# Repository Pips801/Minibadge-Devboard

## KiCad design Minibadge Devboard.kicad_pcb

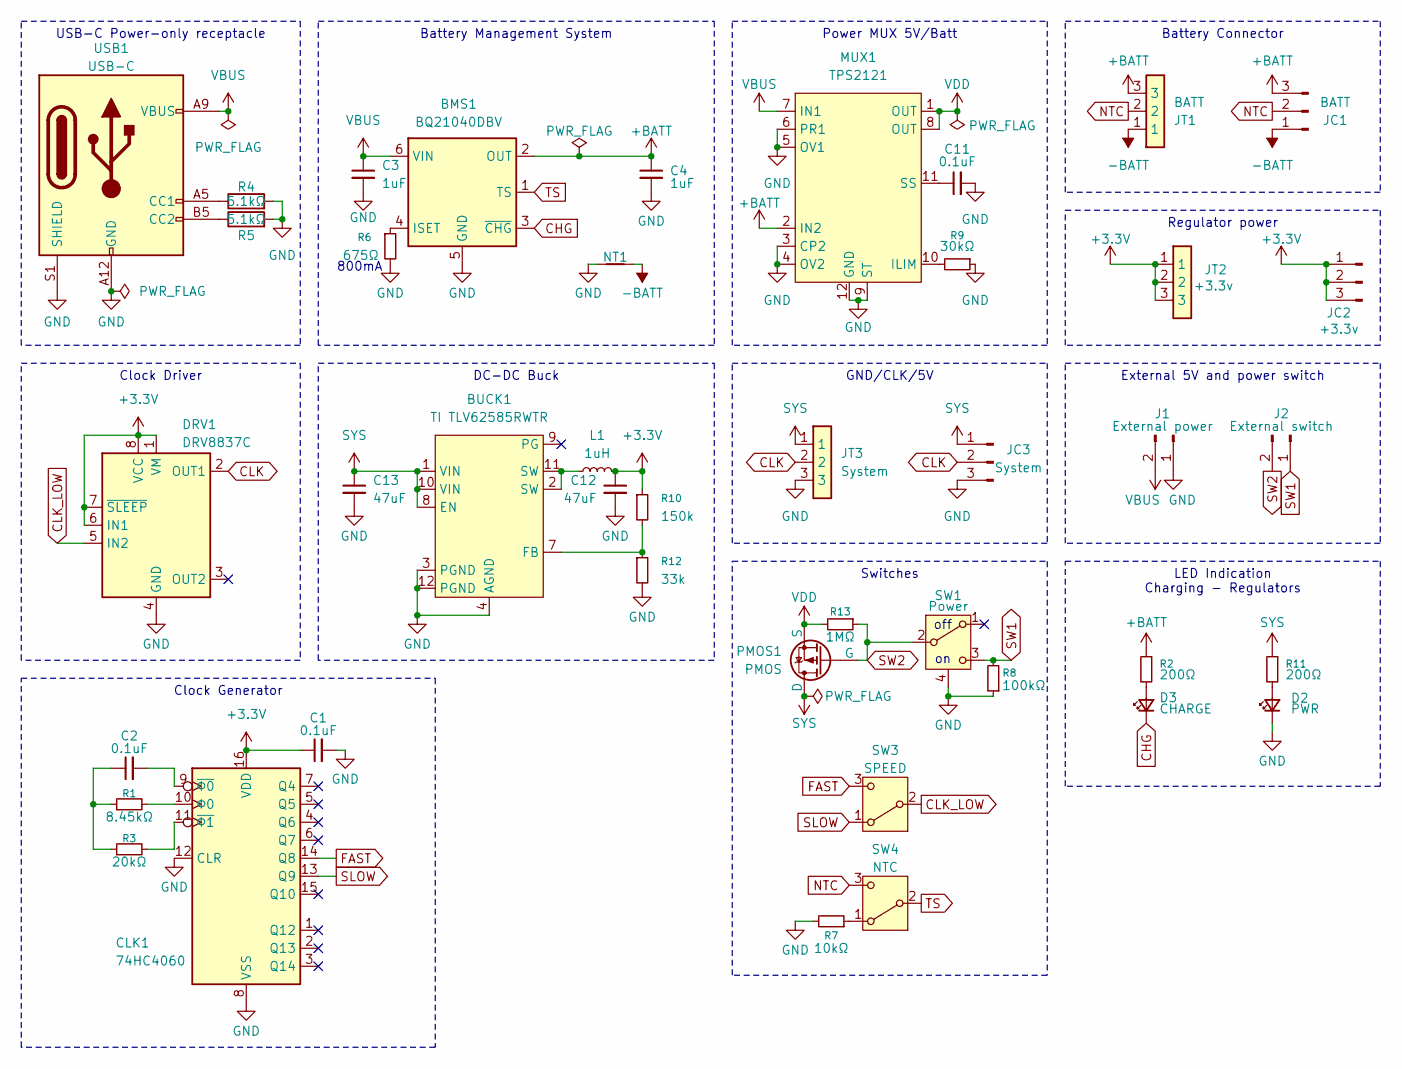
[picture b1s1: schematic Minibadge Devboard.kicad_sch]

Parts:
BMS1: BQ21040DBV; SOT-23-6; LCSC Part # C202311
BUCK1: TI TLV62585RWTR; TLV62585RWTR; LCSC Part # C406872
C1, C2, C11: 0.1uF; C_0603_1608Metric; LCSC Part # C14663
C3, C4: 1uF; C_0603_1608Metric; LCSC Part # C15849
C12, C13: 47uF; C_1206_3216Metric; LCSC Part # C96123
CLK1: 74HC4060; TSSOP-16-1EP_4.4x5mm_P0.65mm; LCSC Part # C354054
D2: PWR; LED_0603_1608Metric; LCSC Part # C2286
D3: CHARGE; LED_0603_1608Metric; LCSC Part # C2286
DRV1: DRV8837C; WSON-8-1EP_2x2mm_P0.5mm_EP0.9x1.6mm; LCSC Part # C191000
J1: External power; Castellated pins 1x02
J2: External switch; Castellated pins 1x02
JC1: BATT; Castellated pins 1x03
JC2: +3.3v; Castellated pins 1x03
JC3: System; Castellated pins 1x03
JT1: BATT; WAGO 2059-303; Manufacturer_Part_Number 2060-453/998-404; LCSC Part # C3309252
JT2: +3.3v; WAGO 2059-303; Manufacturer_Part_Number 2060-453/998-404; LCSC Part # C3309252
JT3: System; WAGO 2059-303; Manufacturer_Part_Number 2060-453/998-404; LCSC Part # C3309252
L1: 1uH; L_KOHERelec_MDA5030; LCSC Part # C2847474
MUX1: TPS2121; Texas_VQFN-HR-12_2x2.5mm_P0.5mm; LCSC Part # C485916
NT1: NetTie_2; NetTie-2_SMD_Pad2.0mm
PMOS1: PMOS; SOT-89-3; LCSC Part # C19272814
R1: 8.45kΩ; R_0603_1608Metric; LCSC Part # C25981
R2, R11: 200Ω; R_0603_1608Metric; LCSC Part # C8218
R3: 20kΩ; R_0603_1608Metric; LCSC Part # C4184
R4, R5: 5.1kΩ; R_0603_1608Metric; LCSC Part # C23186
R6: 675Ω; R_0603_1608Metric; LCSC Part # C23228
R7: 10kΩ; R_0603_1608Metric; LCSC Part # C25804
R8: 100kΩ; R_0603_1608Metric; LCSC Part # C25803
R9: 30kΩ; R_0603_1608Metric; LCSC Part # C22984
R10: 150k; R_0603_1608Metric; LCSC Part # C22807
R12: 33k; R_0603_1608Metric; LCSC Part # C4216
R13: 1MΩ; R_0603_1608Metric; LCSC Part # C22935
SW1: Power; SW-SMD_SK12D07VG3-T; LCSC Part # C25168821
SW3: SPEED; SolderJumper-3_P1.3mm_Open_RoundedPad1.0x1.5mm_NumberLabels; LCSC Part # C5149822
SW4: NTC; SolderJumper-3_P1.3mm_Open_RoundedPad1.0x1.5mm_NumberLabels; LCSC Part # C5149822
USB1: USB-C; USB_C_Receptacle_HRO_TYPE-C-31-M-17; LCSC Part # C283540

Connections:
+3.3V: C1.1, C12.1, CLK1.16 (VDD), DRV1.1 (VM), DRV1.6 (IN1), DRV1.7 (~SLEEP), DRV1.8 (VCC), JC2.1, JC2.2, JC2.3, JT2.1, JT2.2, JT2.3, L1.2, R10.1
+BATT: BMS1.2 (OUT), C4.1, JC1.3, JT1.3, MUX1.2 (IN2), R2.1
-BATT: JC1.1, JT1.1, NT1.2
CHG: BMS1.3 (~CHG), D3.1 (K)
CLK: DRV1.2 (OUT1), JC3.2, JT3.2
CLK_LOW: DRV1.5 (IN2), SW3.2 (B)
FAST: CLK1.14 (Q8), SW3.3 (C)
GND: BMS1.5 (GND), BUCK1.3 (PGND), BUCK1.4 (AGND), BUCK1.12 (PGND), C1.2, C3.2, C4.2, C11.2, C12.2, C13.2, CLK1.8 (VSS), CLK1.12 (CLR), D2.1 (K), DRV1.4 (GND), DRV1.9 (GND), J1.1, JC3.3, JT3.3, MUX1.3 (CP2), MUX1.4 (OV2), MUX1.5 (OV1), MUX1.6 (PR1), MUX1.9 (ST), MUX1.12 (GND), NT1.1, R4.2, R5.2, R6.2, R7.2, R8.1, R9.1, R12.2, SW1.4, USB1.A12 (GND), USB1.B12 (GND), USB1.S1 (SHIELD)
NTC: JC1.2, JT1.2, SW4.3 (C)
unnamed: BMS1.4 (ISET), R6.1
unnamed: BUCK1.7 (FB), R10.2, R12.1
unnamed: BUCK1.2 (SW), BUCK1.11 (SW), L1.1
unnamed: C2.1, R1.1, R3.1
unnamed: C2.2, CLK1.9 (~Φ0)
unnamed: CLK1.11 (~Φ1), R3.2
unnamed: CLK1.10 (Φ0), R1.2
unnamed: D2.2 (A), R11.2
unnamed: D3.2 (A), R2.2
unnamed: MUX1.10 (ILIM), R9.2
unnamed: C11.1, MUX1.11 (SS)
unnamed: R7.1, SW4.1 (A)
unnamed: R4.1, USB1.A5 (CC1)
unnamed: R5.1, USB1.B5 (CC2)
SLOW: CLK1.13 (Q9), SW3.1 (A)
SW1: J2.1, R8.2, SW1.3 (C)
SW2: J2.2, PMOS1.1 (G), R13.1, SW1.2 (B)
SYS: BUCK1.1 (VIN), BUCK1.8 (EN), BUCK1.10 (VIN), C13.1, JC3.1, JT3.1, PMOS1.2 (D), R11.1
TS: BMS1.1 (TS), SW4.2 (B)
VBUS: BMS1.6 (VIN), C3.1, J1.2, MUX1.7 (IN1), USB1.A9 (VBUS), USB1.B9 (VBUS)
VDD: MUX1.1 (OUT), MUX1.8 (OUT), PMOS1.3 (S), R13.2

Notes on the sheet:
800mA
off
External 5V and power switch
USB-C Power-only receptacle
DC-DC Buck
Battery Connector
Battery Management System
Power MUX 5V/Batt
LED Indication Charging - Regulators
GND/CLK/5V
Switches
Clock Driver
Clock Generator
Regulator power

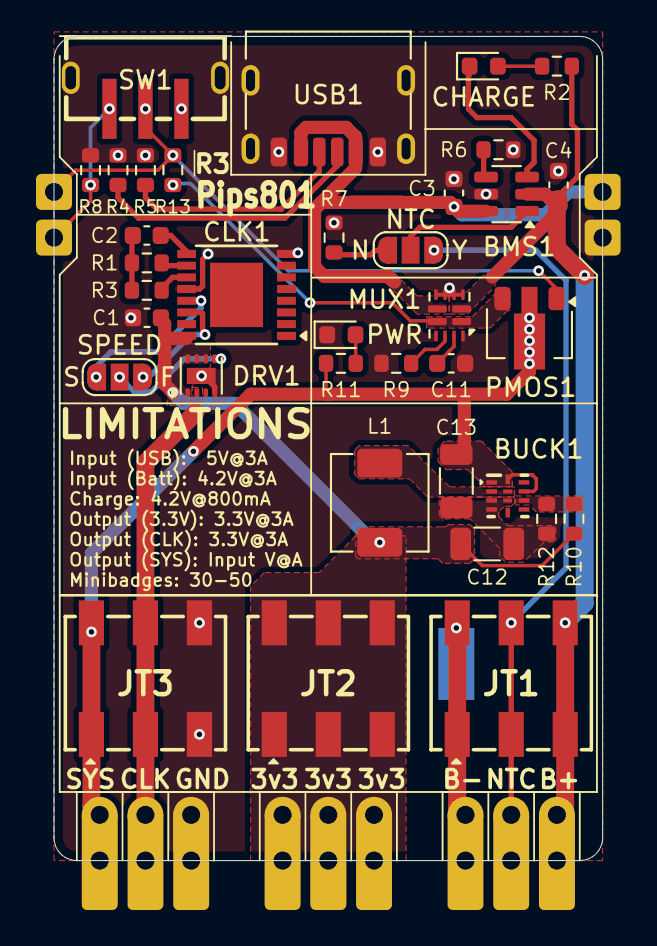
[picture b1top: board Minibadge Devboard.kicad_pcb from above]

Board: 2 copper layers, 30.5 x 45.8 mm, 42 parts (1 on the bottom side), 30 nets.

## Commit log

2025-12-04 Fix SW1
2025-12-07 update PDF
